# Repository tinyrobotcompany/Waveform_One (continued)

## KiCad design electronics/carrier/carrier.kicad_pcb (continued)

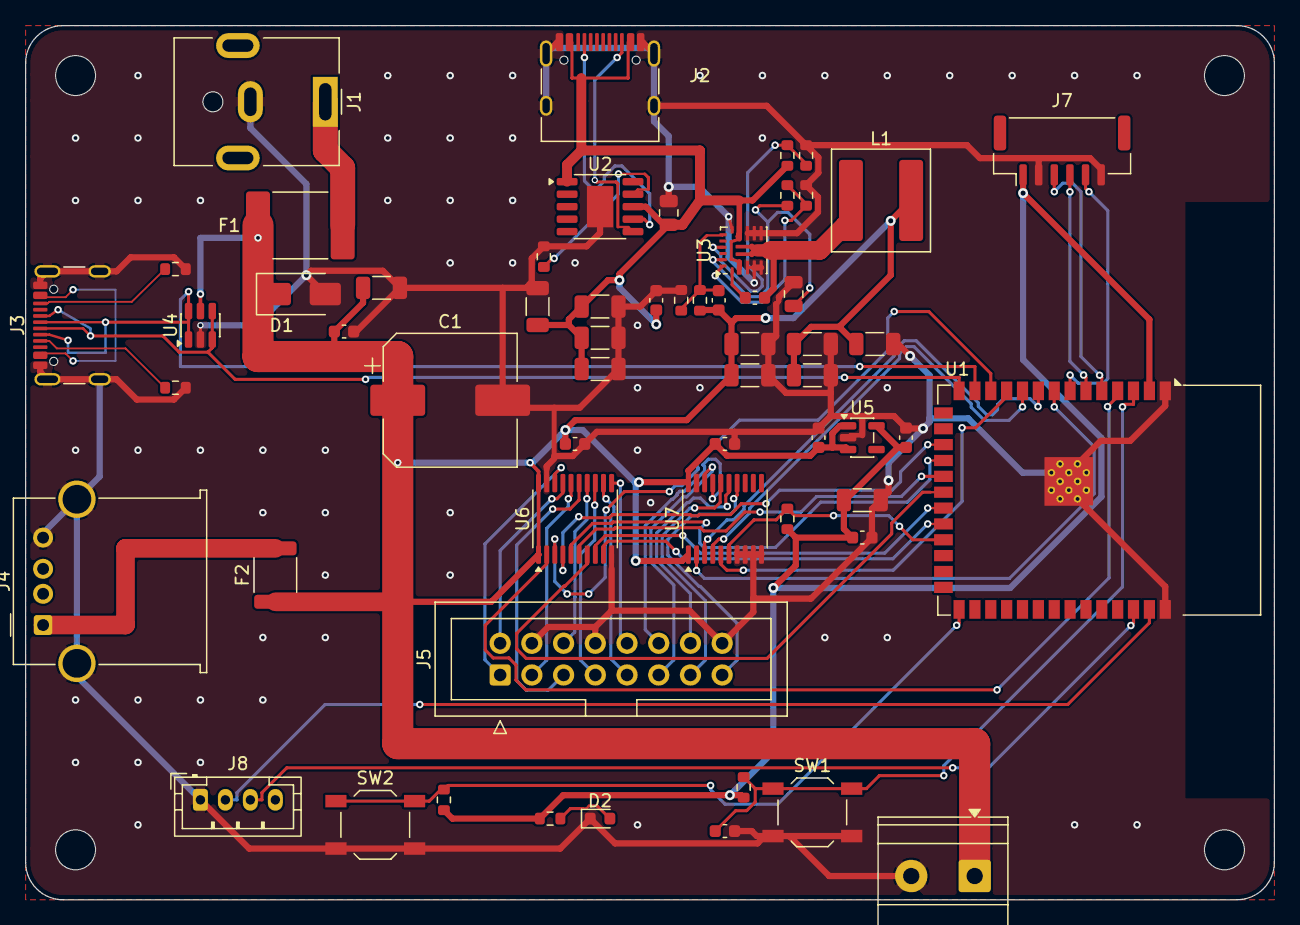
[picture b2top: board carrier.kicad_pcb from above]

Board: 2 copper layers, 100.0 x 70.0 mm, 63 parts (0 on the bottom side), 53 nets.

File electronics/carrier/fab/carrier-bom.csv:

Comment,Designator,Footprint,LCSC Part #
PJ-063AH,J1,BarrelJack_CUI_PJ-063AH_Horizontal,C22434582
6A hold,F1,Fuse_2920_7451Metric,C49318508
SMAJ5.0A,D1,D_SMA,C78401
1000uF 10V,C1,CP_Elec_10x10.5,C165632
22uF 10V,"C2,C5",C_1206_3216Metric,C12891
100nF,"C3,C6,C24,C25",C_0603_1608Metric,C14663
AP2112K-3.3,U5,SOT-23-5,C51118
1uF,"C7,C8,C4",C_0603_1608Metric,C15849
Green,D2,LED_0603_1608Metric,C12624
1k,R5,R_0603_1608Metric,C21190
ESP32-S3-WROOM-1-N16R8,U1,ESP32-S3-WROOM-1,C2913202
10k,"R1,R2,R6",R_0603_1608Metric,C25804
Reset,"SW1,SW2",SW_SPST_TL3342,C2886898
"S3 USB (P4 link, flashing)",J3,USB_C_Receptacle_GCT_USB4105-xx-A_16P_TopMnt_Horizontal,C5184243
5.1k,"R3,R4",R_0603_1608Metric,C23186
USBLC6-2SC6,U4,SOT-23-6,C7519
74AHCT245,"U6,U7",TSSOP-20_4.4x6.5mm_P0.65mm,C173388
HUB75,J5,IDC-Header_2x08_P2.54mm_Vertical,C492443
LED panel 5V,J6,"TerminalBlock_Phoenix_MKDS-1,5-2-5.08_1x02_P5.08mm_Horizontal",C480516
INMP441,J7,JST_GH_BM06B-GHS-TBT_1x06-1MP_P1.25mm_Vertical,C225122
2.5A hold,F2,Fuse_1812_4532Metric,C19078727
5V to P4,J4,USB_A_Molex_67643_Horizontal,C2798029
